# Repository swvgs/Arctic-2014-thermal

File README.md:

Arctic-2014-thermal
===================
For the Eagle files, they are made with Eagle 6.5 FREE. The parts can all be purchased 
from sparkfun except the MLX90614-ACC.

https://www.sparkfun.com/wish_lists/73940

IR Sensor: 35deg FOV
http://www.futureelectronics.com/en/technologies/semiconductors/analog/sensors/temperature/Pages/7012690-MLX90614ESF-ACC-000-TU.aspx?IM=0

IR Sensor: 10deg FOV
http://www.futureelectronics.com/en/technologies/semiconductors/analog/sensors/temperature/Pages/4099248-MLX90614ESF-ACF-000-TU.aspx?IM=0

The v2.0 files would not upload to OSHpark.com correctly (kept showing an old version) so I copied them to another directory, renamed them, uploaded, and it all worked fine. Not sure if it was a caching problem on their end, or something funny on mine.

The code that runs on Whistler is in the code directoy. There is a version that does not give data collection options that is antequaited, please avoid it. The fast version also turns out not to be fast, it was using the digitalWriteFast library to access the pins vai port comands directly, which should have increased the read/write speed by a factor of 10. The code did not show imporvement (mostly becuase the slowness was a factor of the serial port speed more than anything else). Instead of running the different library (which is mostly stable and seems fine) the serial speed was changed from 9600 baud to 57600 baud. This took the loop time from ~20ms to ~3ms. As a happy medium an interval of 5ms was added to ensure a constant data collection rate. This rate will vary between 5ms and 6ms, with an average around 5.1ms (the 6ms is due to the occasional loop that takes slightly longer to run.) It might be possible to get the delay down below the 3ms range with the digitalWriteFast library, but there is no real need for that at this point.

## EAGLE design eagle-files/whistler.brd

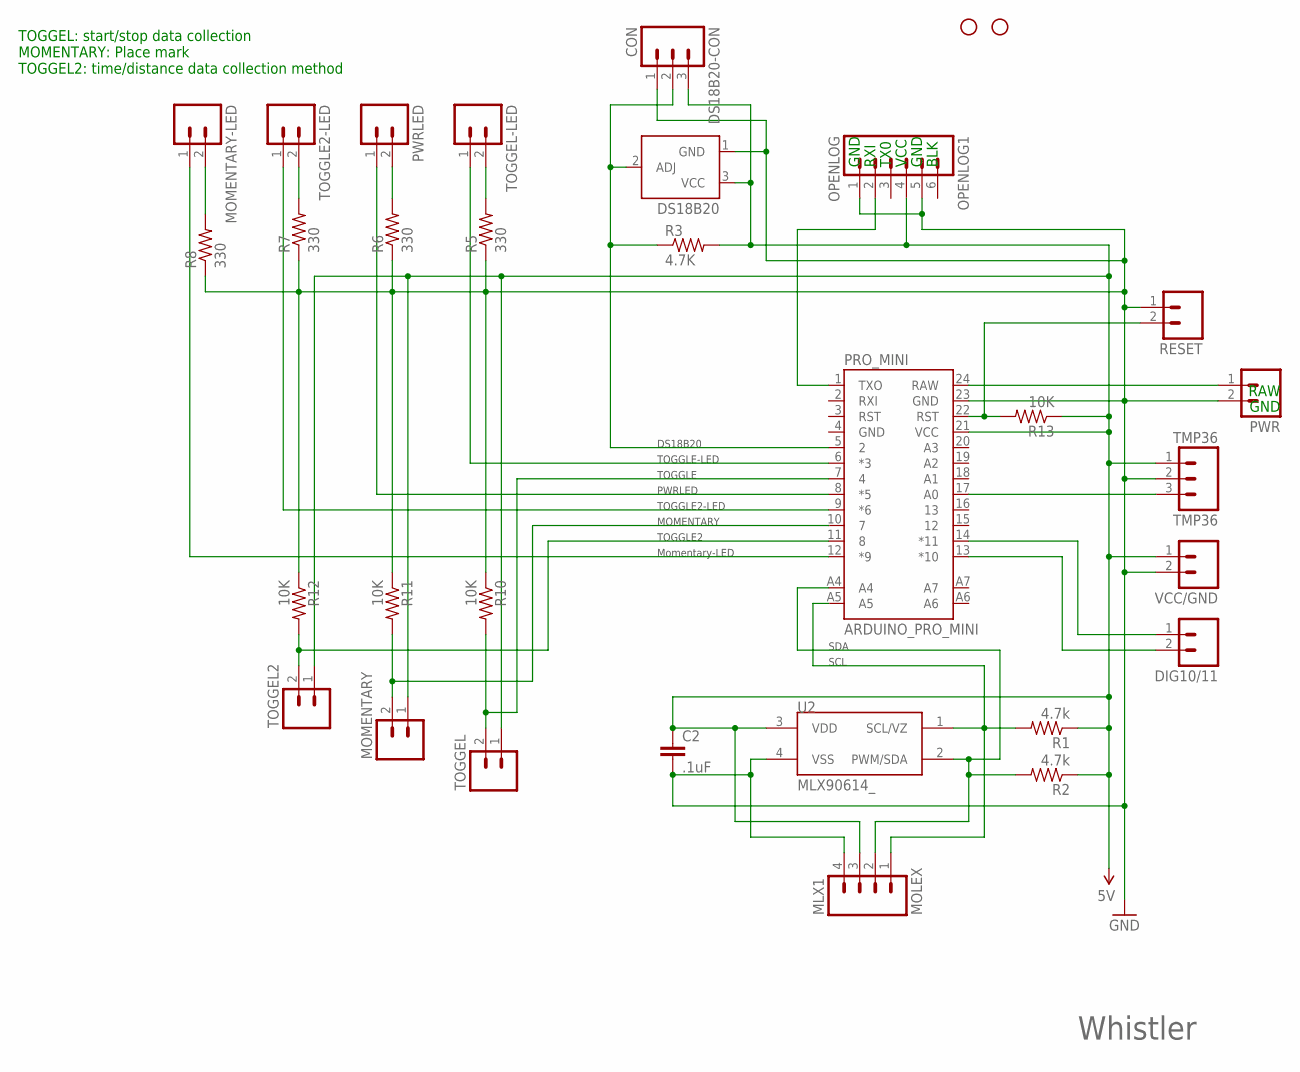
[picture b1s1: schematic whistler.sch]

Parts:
C2: .1uF; CAP-PTH-SMALL-KIT
DIG10/11: M023.5MM_LOCK; SCREWTERMINAL-3.5MM-2_LOCK
DS18B20: TEMPERATURE-SENSOR; TO-92
DS18B20-CON: CON; SCREWTERMINAL-3.5MM-3_LOCK.007S
JP6, JP7: STAND-OFFTIGHT; STAND-OFF-TIGHT
MLX1: MOLEX; 1X04-1MM-RA
MOMENTARY: M023.5MM_LOCK; SCREWTERMINAL-3.5MM-2_LOCK
MOMENTARY-LED: M023.5MM_LOCK; SCREWTERMINAL-3.5MM-2_LOCK
OPENLOG1: OPENLOG; 1X06_LOCK
PRO_MINI: ARDUINO_PRO_MINI
PWR: M023.5MM_LOCK; SCREWTERMINAL-3.5MM-2_LOCK
PWRLED: M023.5MM_LOCK; SCREWTERMINAL-3.5MM-2_LOCK
R1, R2: 4.7k; AXIAL-0.4
R3: 4.7K; AXIAL-0.4
R5, R6, R7, R8: 330; 0603-RES
R10, R11, R12, R13: 10K; 0603-RES
RESET: M023.5MM_LOCK; SCREWTERMINAL-3.5MM-2_LOCK
TMP36: TMP36; SCREWTERMINAL-3.5MM-3_LOCK.007S
TOGGEL, TOGGEL2: M023.5MM_LOCK; SCREWTERMINAL-3.5MM-2_LOCK
TOGGEL-LED: M023.5MM_LOCK; SCREWTERMINAL-3.5MM-2_LOCK
TOGGLE2-LED: M023.5MM_LOCK; SCREWTERMINAL-3.5MM-2_LOCK
U2: MLX90614_; TO-39
VCC/GND: M023.5MM_LOCK; SCREWTERMINAL-3.5MM-2_LOCK

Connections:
5V: C2.1, DS18B20.3 (VCC), DS18B20-CON.3, MLX1.3, MOMENTARY.1, OPENLOG1.4, PRO_MINI.21 (VCC), R1.P$1 (1), R2.P$1 (1), R3.P$2 (2), R13.1, TMP36.1, TOGGEL.1, TOGGEL2.1, U2.3 (VDD), VCC/GND.1
GND: C2.2, DS18B20.1 (GND), DS18B20-CON.1, MLX1.4, OPENLOG1.1, OPENLOG1.5, PRO_MINI.23 (GND), PWR.2, R5.1, R6.1, R7.1, R8.1, R10.1, R11.1, R12.1, RESET.1, TMP36.2, U2.4 (VSS), VCC/GND.2
unnamed: PRO_MINI.7 (4), R10.2, TOGGEL.2
unnamed: DS18B20.2 (ADJ), DS18B20-CON.2, PRO_MINI.5 (2), R3.P$1 (1)
unnamed: DIG10/11.1, PRO_MINI.14 (*11)
unnamed: PRO_MINI.24 (RAW), PWR.1
unnamed: R5.2, TOGGEL-LED.2
unnamed: PRO_MINI.8 (*5), PWRLED.1
unnamed: OPENLOG1.2, PRO_MINI.1 (TXO)
unnamed: MOMENTARY.2, PRO_MINI.10 (7), R11.2
unnamed: DIG10/11.2, PRO_MINI.13 (*10)
unnamed: PRO_MINI.6 (*3), TOGGEL-LED.1
unnamed: PRO_MINI.9 (*6), TOGGLE2-LED.1
unnamed: PWRLED.2, R6.2
unnamed: R7.2, TOGGLE2-LED.2
unnamed: MOMENTARY-LED.2, R8.2
unnamed: MOMENTARY-LED.1, PRO_MINI.12 (*9)
unnamed: PRO_MINI.11 (8), R12.2, TOGGEL2.2
unnamed: PRO_MINI.22 (RST), R13.2, RESET.2
unnamed: PRO_MINI.17 (A0), TMP36.3
unnamed: MLX1.2, PRO_MINI.A4, R2.P$2 (2), U2.2 (PWM/SDA)
unnamed: MLX1.1, PRO_MINI.A5, R1.P$2 (2), U2.1 (SCL/VZ)

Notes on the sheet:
Whistler
GND
RAW
VCC
TX0
RXI
BLK
TOGGEL: start/stop data collection MOMENTARY: Place mark TOGGEL2: time/distance data collection method
TOGGLE
TOGGLE2
MOMENTARY
Momentary-LED
TOGGLE2-LED
PWRLED
TOGGLE-LED
DS18B20
SDA
SCL

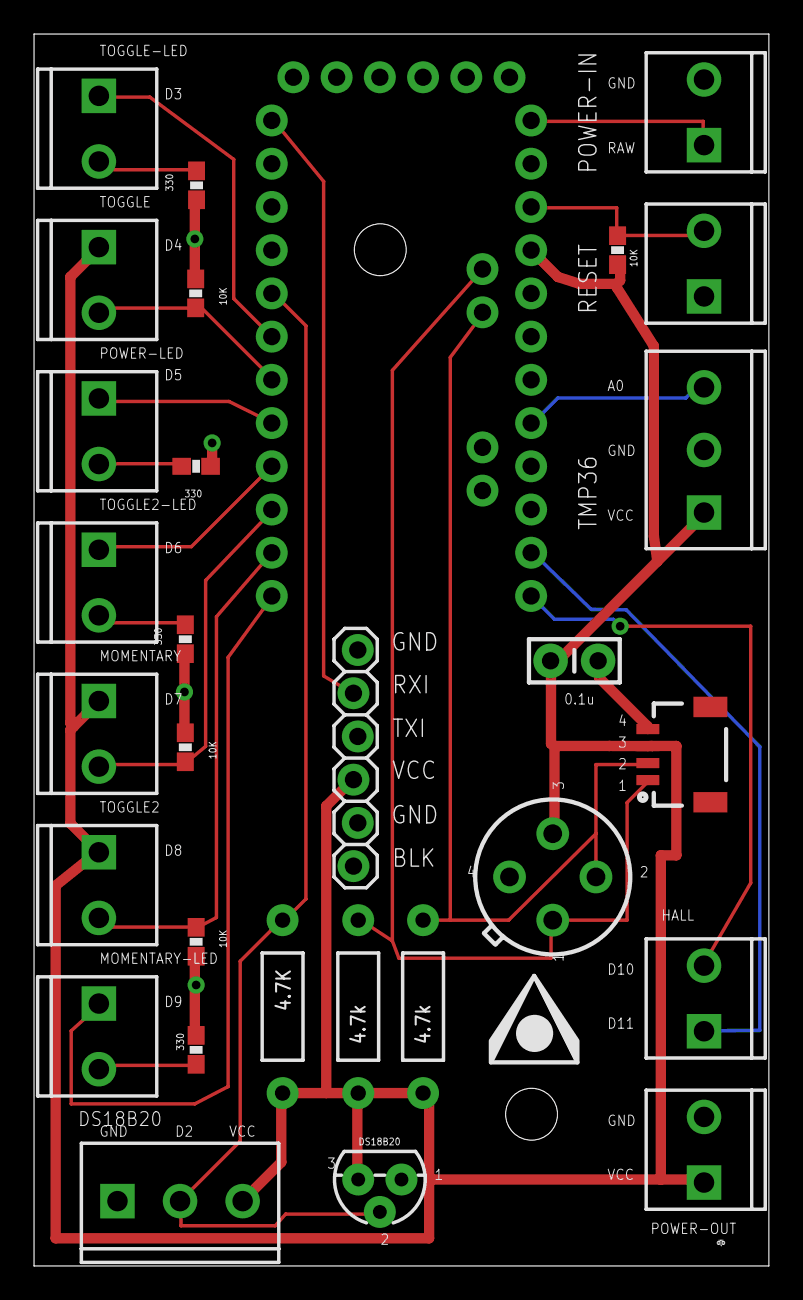
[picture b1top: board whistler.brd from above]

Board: 2 copper layers, 43.2 x 72.4 mm, 32 parts (0 on the bottom side), 22 nets.

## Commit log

2013-07-07 Some data sheets to reference.
2013-11-16 added base files for eagle
2013-11-16 started updating this to new layout.
    added JST 4pin connector. making a sparkfun shopping cart to go with
    this.
2013-11-16 Added all parts to schematic
    Added all the bits and pieces needed to the shcematic and did a rough
    auto route on the board. This is still assuming that the wheel only
    needs 4 pins (power, ground, data1, data2). There is no circuit for
    clean reading for the wheel yet. Have not run DRC or ERC.
2013-11-16 added a few new compnents
    Added compnents and the ground plane. Looking at breaking out the reset
    button, but the pins are all blocked.
2013-11-16 added reset switch and flipped board
    Moved parts around to make more room. I added a reset button, but I am
    not sure it is wired correctly, I need to test it on an Uno to make
    sure that I am not crazy.
2013-11-19 Added an analog hookup.
    Moved a few things, but not much.
2013-11-19 Added shematics
2013-11-19 moved parts around on PCB for better smaller fit
2013-11-29 added sparkfun wishlist as pdf
2013-11-29 added base code for Arduino
2013-12-14 updated txo rxi for eagle
2013-12-14 Added the TMP36 data sheet for the thermal sensor.
2013-12-14 updated and named my analog to tmp36
2013-12-16 Fixed a bunch of errors with the eagle schematic. SLC and SDA were mixed up.
2013-12-17 trying to get files uploaded to OSHpark website. not working. gerber issues and brd issues. nither will work =(
2013-12-19 Played with the eagle board and cleaned it up. Made clearances 12mil for everything.
2013-12-19 re-output the Gerber files so layers can be printed and checked.
2013-12-19 made some revisions to the board layout. Primarly for the silk layers after printing
2013-12-20 Made changes to the whistler.brd and .sch. That is now the primary thing to work from since the v2.0 files pitched a fit when uploading to OSHpark earler.
2013-12-21 Added the oshpark rendered board images.
2013-12-21 MLX90164 hookup picture added
2013-12-30 Added images for whistler parts
2013-12-31 pulled graphs of FOV from MLX90614 datasheet
2013-12-31 Uploaded a rough draft of the whistler intro presentation
2014-01-01 added some misc files that are mostly useless.
2014-01-04 renamed a file and added a TMP36 schematic
2014-01-10 added some test code
2014-01-11 updated the code for testing. Combined the button, hall, TMP36, and MLX90614. Just need to get all the bells and whistles doing exactly what is wanted. All ports check out.
2014-01-12 bogus
2014-01-12 changes to the silk layers in eagle.
2014-01-16 added power cell chip data sheets
2014-01-18 gist with dave
2014-01-19 made the first revision for the code to run Whistler. Also changed some things with the board file, but found out that they were right. hope I did not mess that up.
2014-01-20 writing code to try and segment time based and distance based data logging.
2014-01-21 finished the code for distance or time!
2014-01-21 Digital write fast stuff. might have issue with the whistler_option file, but I think its ok
2014-01-22 trying to fix the code to work with fast reading. no luck. set everything back because I could not find all the errors.
2014-01-22 did testing and found that the digitalWriteFast lib is not faster as far as I can tell. I think this is because it is from 2010, before the ATmega328U2 came out, meaning the port configs it uses are 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
2014-01-22 edited readme
2014-01-22 added some notes on the enclosure
2014-01-24 added a few notes on hole drilling for the enclosure
2014-01-30 some enclosure things
2014-01-30 enclosure stuff
2014-02-09 working on python basic code. added gitignore. uploaded a raw data file. changed structure of the distance text output.
2014-02-09 played with python, made some data files. gaining basic control now.
2014-02-09 added commends to the python files
2014-02-09 made a bumpy version of the python.
2014-03-02 updated the python code so that it would do standard deviation
2014-03-05 added a thing that writes files
2014-03-05 forgot to save
2014-03-06 fixed the code to do some things and fixed corey. that should teach him.
2014-03-06 changes changes changes
2014-03-06 made something do something.
2014-03-07 processed some stuff.
2014-03-11 played with rwsidt.py. no dice

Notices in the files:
parts and their libraries:
SparkFun-Connectors: Licensing: CC v3.0 Share-Alike You are welcome to use this library for commercial purposes.
